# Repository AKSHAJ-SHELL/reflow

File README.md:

# reflow

**An early AI PCB design agent with a verifier that checks its work.**

You describe a small board. An AI drafts it. A verifier written by a person, not by the AI, checks the draft and explains every mistake in plain English. The AI never picks a part number.

> **This is an alpha.** It handles simple, low-speed boards, and it has real gaps. Read [Limits](#limits) and [Risks](#risks) before trusting anything it makes.

## This project grows as I learn

I'm learning electronics while I build this, and reflow only knows what I understand well enough to write a check for. The more I learn, the more the base of reflow will reflect it.

| Stage | What reflow can check | State |
|---|---|---|
| Low-speed boards: I²C sensors, EEPROMs, LEDs | connections, datasheet pin maps, decoupling and pull-ups | **built, and limited** |
| Power and analog: current limits, trace width, heat | | planned |
| High-speed and RF: impedance, return paths, length matching | | planned |
| FPGA boards: power sequencing, many rails, BGA | | planned |
| Chip design (Verilog) | whether the verifier-first idea carries over at all | an idea, not decided |

Anything marked planned doesn't exist yet. If you know more than I do, corrections are the most useful thing you can send.

## What works today

| Part | What it does | State |
|---|---|---|
| `reflow check` | Checks any KiCad schematic for 5 kinds of mistake | works |
| `reflow design` | Model → board code → compile → verify → fix, up to 3 attempts | works on simple boards |
| Part resolver | Finds real parts in a local copy of the JLCPCB catalog | works; some of it is awaiting my review |
| `reflow tui` | The guided way to design a board, step by step | new; one full run so far |
| `reflow learn` | Find the AI's bug in a local web app, run two circuit simulations, sign off | works; simulations awaiting my review |
| `reflow export` | Runs KiCad DRC, then writes gerbers, drill, placement and BOM | works; often refuses (see Limits) |
| `reflow report` | Writes up every attempt, error and sign-off | works |

**What has actually been tested:**
- **Eval, 2026-10-28:** 5 simple boards × 3 runs, on one model (Sonnet, through Claude Code). 12 of 15 runs gave a verifier-clean board on the first attempt, with 0 part numbers from outside the resolver. The AMS1117 regulator failed all 3. An AI agent drafted the boards' expected results and I checked them on 2026-10-31, after this run, so this run's file still says `undecided`. It's a progress check on simple boards I chose, not a benchmark. The results: [evals/results/20261028T161716Z.json](evals/results/20261028T161716Z.json).
- **One real run through the TUI, 2026-11-06:** an INA226 power monitor ([boards/opi-power-demo](boards/opi-power-demo)). It went from a prompt to a verifier-clean schematic on the first attempt, with 0 KiCad ERC violations, and an electrical mentor looked over the schematic informally. It hasn't been routed, exported or built, and its `rules.toml` wasn't enforced (see Limits).
- **No board designed by reflow has been fabricated and tested yet.**

## Try it: check a schematic (5 minutes, macOS)

You need [Homebrew](https://brew.sh). No AI or API key is involved in this part.

```bash
brew install --cask kicad
brew install uv
git clone https://github.com/AKSHAJ-SHELL/reflow
cd reflow
uv venv --python 3.14 .venv
source .venv/bin/activate
uv pip install -e .
```

Run it on a board with a planted bug, then on a good one:

```bash
reflow check fixtures/bad_series_cap
```

```bash
reflow check fixtures/sensor_good
```

The first one reports:

```
✗ ERROR  decoupling.series   C1, U1
  C1 sits in series between +3.3V and U1.8; U1 only gets power through a
  capacitor, which blocks DC.
  why:  A capacitor blocks DC, so the chip never gets steady power and won't
        turn on. Decoupling caps go in parallel, power to ground, to absorb fast
        current spikes at the chip.
  fix:  Connect U1.8 directly to +3.3V, then rewire C1 so one pin is on +3.3V
        and the other is on GND.
```

Then point it at your own board:

```bash
reflow check path/to/your/board.kicad_sch
```

## Design a board

**One-time setup.** Run these from the `reflow` folder (every tool and setting is in [SETUP.md](SETUP.md)):

```bash
brew install node oven-sh/bun/bun
npm ci --prefix tools/tscircuit
export PATH="$PWD/tools/tscircuit/node_modules/.bin:$PATH"
uv pip install -e '.[learn,tui]'
reflow parts update    # downloads the JLCPCB parts catalog, about 1.5 GB
```

The `export PATH` line lasts for one terminal session. Add it to `~/.zshrc`, with the full path, to keep it.

You also need [Claude Code](https://claude.com/claude-code), installed and logged in. reflow uses your login, so no API key is needed.

**Then make a folder for your board and open reflow there:**

```bash
mkdir -p ~/boards/my-board && cd ~/boards/my-board && reflow tui
```

The screen walks you through it, with an AI helper on the right you can ask anything:

1. **Say what you want,** and type the exact part number of the main chip. reflow never picks one for you.
2. **Drag in the chip's datasheet PDF.** The helper can then search it and cite pages.
3. **Draft the plan** and answer its questions. Press **Re-plan with my answers** until it's right, then **Accept plan**.
4. **Write your `rules.toml`:** one rule for each thing the datasheet asks for. reflow gives you a template and checks it. Ask the helper if a section confuses you.
5. **Run the design.** The AI gets up to 3 attempts.
6. **Run `reflow check`.** If it fails, open it in KiCad and learn mode, work out what went wrong, type the fix and run it again.

**← Back** (or Ctrl+B) goes back a step, and Ctrl+Q quits. Everything is saved in the folder, so you can close it and pick up later.

## All commands

| Command | What it does |
|---|---|
| `reflow check PATH` | Check a `.kicad_sch`, a `.kicad_pro` or a project folder. Add `--json` for JSON, or `--strict` to fail on warnings. |
| `reflow tui [FOLDER]` | Design a board step by step. Needs `[tui]` and Claude Code. |
| `reflow design --spec S --plan P --run-dir D` | Design without the TUI, from a spec and plan you wrote. |
| `reflow learn RUN` | Open a finished run in your browser: find the bug, simulate, sign off. Needs `[learn]`. |
| `reflow export RUN` | Run DRC and write fab files to `RUN/out`. |
| `reflow report RUN` | Write `report.md` and `report.json` for a run. |
| `reflow rules check FILE` | Check a `rules.toml` against its parts' pins. |
| `reflow parts update` | Download or refresh the JLCPCB parts catalog. |
| `reflow eval` | Run the eval boards. Add `--only NAME` for one, or `--repeat N`. |

`reflow check` exits `0` when clean, `1` on errors, and `2` for a tool or input problem. Add `--help` to any command for the details.

**Without the TUI**, each folder in `evals/` has a ready spec and plan:

```bash
reflow design --spec evals/mcp9808_breakout/spec.json --plan evals/mcp9808_breakout/plan.json --run-dir runs/mcp9808
```

```bash
reflow learn runs/mcp9808
```

```bash
reflow export runs/mcp9808
```

To use an API instead of Claude Code, see [SETUP.md](SETUP.md#3-a-model).

## Limits

**What it can design**
- **Simple, low-speed, 2-layer boards only:** I²C sensors, EEPROMs, LEDs, a regulator, about 20 parts.
- **Microcontrollers, USB, DDR, Ethernet and RF are out.** There's no high-speed check of any kind.
- **Regulators are shaky.** The AMS1117 failed every eval run on a pin-map question that's still open.

**What the checks miss**
- **"Passed" is a narrow claim.** It means the board compiled and has no violations of the few rules below. It doesn't mean the board works.
- **Only 5 kinds of schematic mistake are caught** (`decoupling.series`, `decoupling.missing`, `i2c.missing_pullup`, `i2c.duplicate_pullup`, `address.floating`), plus pin-map errors on AI boards and one draft rule (`i2c.pullup_rail`). It doesn't replace KiCad's ERC and DRC; run both.
- **Your `rules.toml` doesn't fail a board yet.** The AI is told your rules, but nothing checks the board against them. A board can say `passed` while breaking one (task R-10).
- **I²C checks find the bus by pin name.** A chip that names its pins differently, like the LIS3DH's `SPC`/`SDI`, skips those checks without telling you.
- **No SPI or UART checks.**
- **No current, heat or analog layout checks.** Trace width and Kelvin connections aren't checked. Check them in KiCad.
- **Only two simulations exist** (decoupling and I²C rise time). They use assumed values, shown next to each graph.

**Parts**
- **JLCPCB catalog only.** You can't use another vendor's library yet.
- **The catalog is a snapshot,** so stock and prices can be out of date.

**Routing and platform**
- **Routing is tscircuit's autorouter.** It sometimes breaks a length limit or can't finish, and then `reflow export` refuses. That's deliberate.
- **KiCad 10, single-sheet schematics.** The full flow has only been run on macOS.

## Risks

- **Don't order a board on reflow's word.** Review the schematic and layout yourself against the datasheets. A wrong board costs money and can damage whatever it's plugged into.
- **The AI's code runs on your computer** with your permissions. Its board code is compiled locally as tscircuit TSX, and it isn't sandboxed yet. If you use an API key, that code could reach it (task CI-06). Don't run reflow on a machine holding secrets you can't afford to lose. Details: [docs/REVIEWING.md](docs/REVIEWING.md#4-known-risks-in-the-code-today).
- **Your data goes to the model provider.** Your request, plan and answers, and the parts of your datasheet the helper reads, are sent to Claude or whichever API you set. Don't use it on confidential designs.
- **The local learn server has a known gap.** It only listens on your own machine, but it doesn't check the Host header yet, so a malicious website could try to reach it while it's running (task CI-07). Close it when you're done.
- **AI usage counts against your account.** Runs use your Claude Code plan or your API credits.
- **Some code hasn't had a full human review.** I hand-wrote the core rules and design loop, and AI agents wrote much of the plumbing. Items marked *awaiting human review* in [TASKS.md](TASKS.md) are agent-written and not yet signed off: the resolver's category logic, pin binding, the simulation testbenches and `i2c.pullup_rail`.
- **Expect breaking changes.** File formats and commands can change between versions.

## How it works

```
your request + datasheet ─▶ plan (you confirm) ─▶ part resolver (JLCPCB catalog)
        ─▶ AI writes board code ─▶ compile ─▶ VERIFIER ──fail, up to 3 tries──▶ back to the AI
                                                  │ pass
                                                  ▼
                 you review and sign off ─▶ route check + DRC ─▶ gerbers · BOM · schematic · report
```

More detail: [docs/02-architecture.md](docs/02-architecture.md).

## Folder guide

| Path | What's there |
|---|---|
| `reflow/` | The package: CLI, compile, verifier, routing check, export, TUI |
| `reflow/rules/` | The verifier's rules, one file per family |
| `reflow/harness/` | The design loop: attempts, feedback to the model, when to stop |
| `reflow/parts/` | Parts catalog, resolver, KiCad pin maps |
| `reflow/learn/` | Learn mode's server (`web/` is its source) |
| `prompts/` | The model prompts, as files |
| `boards/` | Sample board projects, including the INA226 demo |
| `evals/` | The boards the design loop is measured on |
| `fixtures/` | KiCad boards with known answers; one planted bug per bad board |
| `tests/` | Tests for every stage |
| `docs/` | Design docs, read in order 00 → 08 |
| `TASKS.md`, `PROGRESS.md` | What's planned, and a log of what happened, including failures |

## Contributing

- **Send a board that died.** Open an issue with the KiCad files and what went wrong. It could become a fixture and maybe a rule.
- **Tell me what's wrong.** Mistakes in the rules or in this README are the most useful reports.
- Plumbing PRs (CLI, exporters, API clients) are welcome. [AGENTS.md](AGENTS.md) has the rules every contributor, human or AI, follows. Never weaken a test to make it pass.

## License

**reflow doesn't have a license yet,** so for now no one else has permission to reuse the code. I plan to open-source it and will add a `LICENSE` file when I've chosen one.

reflow is an independent project, not affiliated with any commercial PCB tool.

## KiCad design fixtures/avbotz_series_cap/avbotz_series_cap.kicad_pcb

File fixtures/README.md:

# fixtures/: boards with known answers (OWNER: HUMAN)

Each folder is a KiCad project (`<name>.kicad_sch/.kicad_pro/.kicad_pcb`) plus `expected.toml`:

```toml
violations = ["decoupling.series"]      # exact set of rule IDs; [] for good boards
pin_net  = { "U1.4" = "GND" }           # optional hand-checked nets
same_net = [["J1.2", "U1.1"]]           # optional
```

Good: `blinky_good`, `sensor_good`. Bad (one planted bug each): `bad_series_cap`, `bad_no_pullups`, `bad_floating_addr`.

**Make one:** `tools/new_fixture.sh <src> <dst>`, open via the `.kicad_pro`, plant one bug, write `expected.toml`.

**Must never:** be created, edited or deleted by an agent; contain more than one planted bug; be opened by double-clicking the `.kicad_sch` (creates "Untitled" files).

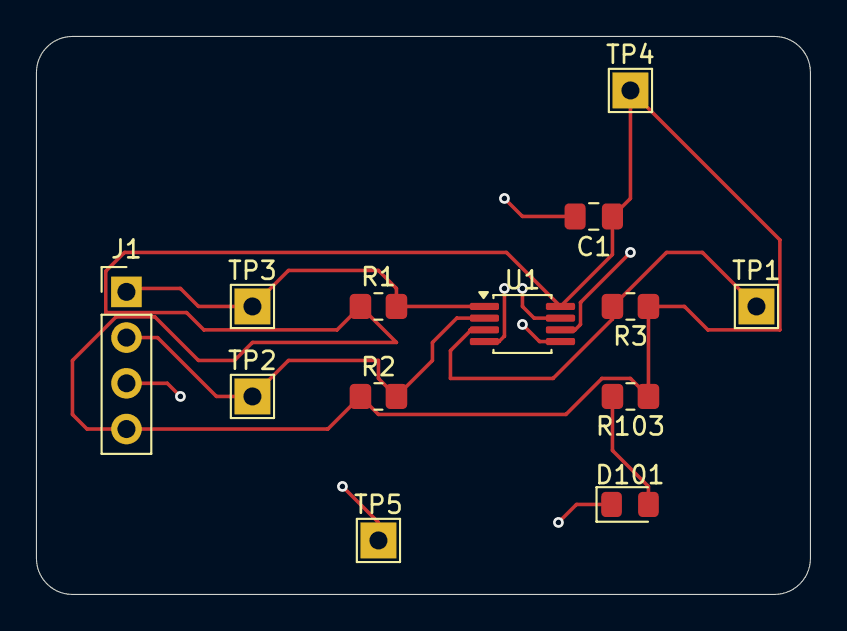
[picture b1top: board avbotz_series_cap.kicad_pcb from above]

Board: 2 copper layers, 43.0 x 31.0 mm, 13 parts (0 on the bottom side), 6 nets.

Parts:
C1: 0.1uf; C_0805_2012Metric_Pad1.18x1.45mm_HandSolder
D101: 3v3_red; LED_0805_2012Metric_Pad1.15x1.40mm_HandSolder
J1: Conn_01x04_Pin; PinHeader_1x04_P2.54mm_Vertical
R1, R2: 4k7; R_0805_2012Metric_Pad1.20x1.40mm_HandSolder
R3: 10k; R_0805_2012Metric_Pad1.20x1.40mm_HandSolder
R103: 270R; R_0805_2012Metric_Pad1.20x1.40mm_HandSolder
TP1, TP2, TP3, TP4, TP5: TestPoint; TestPoint_THTPad_2.0x2.0mm_Drill1.0mm
U1: MCP9808_MSOP; MSOP-8_3x3mm_P0.65mm

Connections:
+3.3V: C1.1, J1.4, R1.1, R2.1, R3.1, R103.1, TP4.1 (1_1), U1.8 (V_{DD})
/SCL: J1.2, R2.2, TP2.1 (1_1), U1.2 (SCL)
/SDA: J1.1, R1.2, TP3.1 (1_1), U1.1 (SDA)
GND: C1.2, D101.1 (K), J1.3, TP5.1 (1_1), U1.4 (GND), U1.5 (A2), U1.6 (A1), U1.7 (A0)
unnamed: D101.2 (A), R103.2
unnamed: R3.2, TP1.1 (1_1), U1.3 (Alert)

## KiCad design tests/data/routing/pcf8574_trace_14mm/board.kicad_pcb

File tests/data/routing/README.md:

# Routing inputs (X-01, X-04)

`mcp9808_fixed.tsx`: the MCP9808 eval board as fixed in learn mode (the real AI draft of eval run
20261022T193720Z, attempt 1, relabelled to the datasheet pinout and wired; it verifies clean).

tscircuit's autorouter runs inside `tsci export`. It gives a decoupling cap's traces a 1 mm
maximum length (`DEFAULT_MAX_DECOUPLING_TRACE_LENGTH_MM` in @tscircuit/core), and skips routing
the whole board when automatic placement leaves the cap farther than that from the pin. As
written, this board doesn't route. With `maxDecouplingTraceLength="3mm"` on C1, every connection
routes and C1's trace to VDD is 2.89 mm. With 2 mm it still doesn't route (tsci 0.0.2768).

2026-10-27: the limit covers both of a decoupling cap's traces, including its ground side to the
nearest GND pad. With 3 mm, placement missed by about 0.5 mm on 3 of 5 eval boards
(run 20261028T004800Z: 3.46–3.56 mm), and routing was skipped. The codegen prompt now asks for 5 mm.

Hole-clearance inputs (2026-10-27), exported .kicad_pcb files from real eval runs (Sonnet 5.5):
- `at24c02_via_0198mm.kicad_pcb` (run 20261028T010434Z): a via 0.198 mm from the SCL track. Under
  JLCPCB's "Via hole to Track" 0.2 mm this is a real violation.
- `ams1117_via_0216mm.kicad_pcb` (same run, attempt 2): a via 0.216 mm from U1 pad 1. It passes
  JLCPCB's 0.2 mm via rule; KiCad's 0.25 mm default flagged it.
- `mcp9808_routed_headers.kicad_pcb` (run 20261028T004800Z): routed, with J1's plated through-holes
  next to tracks (closest 1.25 mm), used to show the PTH rule applies to PTH pads.

Board-size input (2026-10-27): `pcf8574_40x30.tsx` is the PCF8574 eval draft from run
20261028T010434Z (Sonnet 5.5, attempt 1), unchanged. The model drew a 40 x 30 mm board and set
pcbX/pcbY by hand; J1 sits 0.56 mm and J2 4.64 mm past the edge, and tscircuit skipped routing
for the placement errors. With `<board>` (no width or height) and no pcbX/pcbY, tscircuit places
the parts and sizes the board around them (23.28 x 21.875 mm, tsci 0.0.2768), every part sits
inside the edge, and all 12 nets route. Our DRC still finds 2 router vias under JLCPCB's 0.2 mm
via-to-track rule on that board. Keeping the model's placement with no size also fits, but its
decoupling traces come out 8.35 and 8.98 mm, over the 5 mm limit. So the codegen prompt asks for
no size (unless the spec gives one) and no hand placement.

Via inputs (2026-10-27): `at24c02_draft.tsx` (run 20261028T010434Z) and `pcf8574_unsized.tsx`
(run 20261028T025622Z) are real Sonnet 5.5 drafts, unchanged. tscircuit's vias are 0.3 mm on a
0.2 mm drill, and the router keeps ~0.1 mm of copper from a via to a track, so the hole lands
0.198 mm (AT24C02) and 0.159 mm (PCF8574) from a track, under JLCPCB's 0.2 mm. The PCF8574 also
reports a 0.1651 mm via on some runs, not all. With `minViaPadDiameter="0.4mm"` on the board
(0.1 mm ring), both route with 0 DRC errors, 4 of 4 runs each, and the MCP9808, AMS1117
attempts 1–3 and LED boards still route with 0 errors.

Trace-length inputs (2026-10-28), exported boards from run 20261028T161716Z (Sonnet 5.5), each
folder holding circuit.json, board.kicad_pcb, board.kicad_pro, board.kicad_dru and the draft TSX,
unchanged: every net is copper and our DRC has 0 errors, but tscircuit's
`pcb_trace_too_long_error` says a decoupling cap's trace is over the 5 mm asked for.
- `mcp9808_trace_6mm/` (run 3): C1.pin1 to J1.pin1 on V3_3, 6.05 mm.
- `pcf8574_trace_14mm/` (run 2): C1.pin2 to U1.A0 on GND, 14.01 mm (the cap's ground side; U1.A0
  is tied to GND for address 0x20).

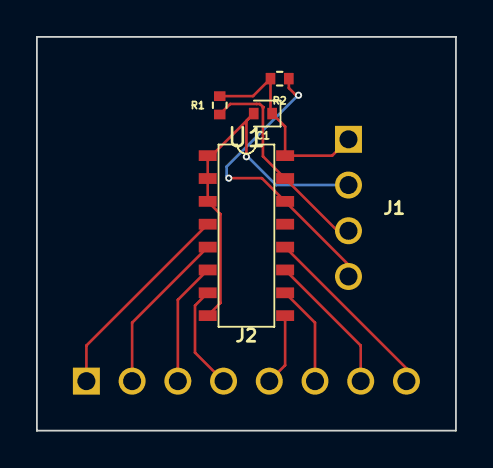
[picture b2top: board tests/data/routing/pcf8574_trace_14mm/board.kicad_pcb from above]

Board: 2 copper layers, 23.3 x 21.9 mm, 6 parts (0 on the bottom side), 12 nets.

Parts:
C1: 100nF; CL05B104KB54PNC
J1: J1; HX_PZ2_54-1x4P_ZZ
J2: J2; PZ254V-11-08P
R1, R2: 4.7kΩ; 0402WGF4701TCE
U1: PCF8574T/3,518; PCF8574T_3_518

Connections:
GND: C1.2, J1.2, U1.1, U1.2, U1.3, U1.8
P0: J2.1, U1.4
P1: J2.2, U1.5
P2: J2.3, U1.6
P3: J2.4, U1.7
P4: J2.5, U1.9
P5: J2.6, U1.10
P6: J2.7, U1.11
P7: J2.8, U1.12
SCL: J1.4, R2.1, U1.14
SDA: J1.3, R1.1, U1.15
V3_3: C1.1, J1.1, R1.2, R2.2, U1.16

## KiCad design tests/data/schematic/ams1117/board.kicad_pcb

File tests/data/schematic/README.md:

# Schematic inputs (O-04)

Real boards from `reflow eval --repeat 3` run 20261028T161716Z (Sonnet 5.5), run 1 of each eval:
the attempt's `circuit.json`, `board.kicad_pcb` and `board.kicad_pro` from its build folder, and a
copy of the eval's `rules.toml` (its `[[part]]` names each chip's KiCad symbol). Unchanged.

- `mcp9808/`, `pcf8574/`, `at24c02/`: attempt 1, verify clean. Our schematic of each has 0 KiCad ERC
  errors and 0 warnings, `reflow check` on it is clean, and its nets are circuit.json's and the PCB's.
- `pcf8574/tscircuit.kicad_sch`: tscircuit's own export of the same board. KiCad ERC finds 21 errors
  and 87 warnings (wire ends 0.06–0.09 mm short of pins, off the 1.27 mm grid; invented symbol
  libraries), J2 and P0–P7 are disconnected, and GND is split in two.
- `led/`: attempt 1. tscircuit's LED has the anode on pad 1; KiCad's LED symbol has the cathode on
  pin 1, so the schematic is refused (the KT-0603R cathode pad is a TO CHECK line in expected.toml).
  No rules.toml: the eval has none.
- `ams1117/`: attempt 3. The board's U1 has pin 4 (the tab); KiCad's AMS1117-3.3 has 3 pins (V-12).

kicad-cli writes `.kicad_prl` next to what it opens, so tests work on copies.

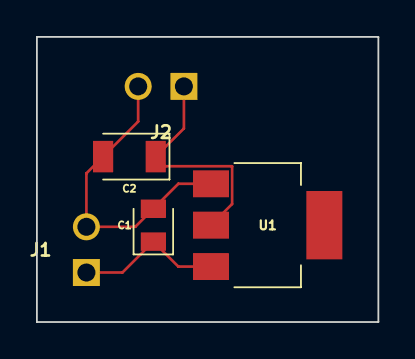
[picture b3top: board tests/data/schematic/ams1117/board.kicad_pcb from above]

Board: 2 copper layers, 19.0 x 15.8 mm, 5 parts (0 on the bottom side), 3 nets.

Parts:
C1: 10uF; CL21A106KAYNNNE
C2: 22uF; CL31A226KAHNNNE
J1: J1; PZ254V-11-02P
J2: J2; PZ254V-11-02P
U1: AMS1117-3.3; AMS1117-3_3

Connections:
GND: C1.2, C2.2, J1.2, J2.2, U1.1
V3_3: C2.1, J2.1, U1.2
V5: C1.1, J1.1, U1.3

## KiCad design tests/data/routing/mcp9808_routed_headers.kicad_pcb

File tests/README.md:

# tests/

| File | What | Needs KiCad |
|---|---|---|
| `conftest.py` | Finds every fixture, exports a fresh netlist per test | yes |
| `test_netlist.py` | Invariants + hand-checked nets + expected violations per fixture | yes |
| `test_cli.py` | `reflow check` exit codes and output | yes (skips if missing) |
| `test_catalog.py` | `parse_value`, `CatalogPart` defaults, and that the jlcsearch client and cache are gone | no |
| `test_contracts.py` | Frozen schemas, strict example parsing, stub honesty | no |
| `test_circuit_netlist.py` | `circuit.json` → `Netlist` on recorded boards (`data/circuit_json/`), the rules on that netlist, and malformed input | no |
| `test_pcb_nets.py` | `.kicad_pcb` pad nets: tscircuit export vs its `circuit.json`, syntax and error cases | no |
| `test_pinmap.py` | Pin maps from ST pin data and KiCad symbols (`data/pinmaps/`, licences beside them): MCP9808 vs its datasheet, STM32F103C8 across sources, disagreement reporting | installed-library case only (skips if missing) |
| `test_verifier.py` | The design verifier on recorded `circuit.json` boards: report shape, required `bind`, refuses `.kicad_sch` | no |
| `test_design_wiring.py` | `reflow design` from config: scripted model, real tsci and verifier, fake catalog; config and catalog errors | tsci for the end-to-end cases (skips if missing) |
| `test_parts_snapshot.py` | `reflow parts update` on a six-part split-archive fixture (`data/snapshot/`) over file:// URLs: install, CRC and format checks, old database kept on failure | no |
| `test_local_catalog.py` | Local-snapshot queries on 27 real rows (`data/parts_db/`): values, tolerance, voltage, headers, MPN prefix, category mapping, the MCP9808 plan through the resolver | no |
| `test_evals.py` | Structure of every `evals/` board: strict spec and plan, named parts verbatim in the request, D-6a headers, expected.toml agrees with the plan | no |
| `test_eval_runner.py` | The eval runner with a scripted model, real tsci and verifier, and the parts fixture: pass rates, foreign part numbers, expectation misses, errors, go/no-go, results file, `reflow eval` | tsci (skips if missing); about 2 minutes |
| `test_project_rules.py` | `rules.toml` parsing and `reflow rules check`: required why/source, field errors, unknown pins, uncovered power/reset/boot pins | no |
| `test_rules_prompt.py` | Project rules rendered for the codegen/fix prompts (no why/source), `reflow design` resolving and checking `rules_file`, `[[part]]` pin maps in `reflow rules check`; one test is red until `docs/proposals/V-22-loop-HUMAN.patch` is applied | no |
| `test_pinbind.py` | V-12 pin binding on the first real board (`data/real_runs/`): its wrong MCP9808 pinout is reported pin by pin, the corrected board binds clean, bound power pins let decoupling run, unidentified / unmapped chips are errors | no |
| `test_integration.py` | Real tsci + kicad-cli + rules, and the design loop with a scripted model (inputs in `data/integration/`) | yes, and tsci (skips if missing) |

Run: `pytest -q`. **Never weaken a test** (docs/agents/04-testing-rules.md).

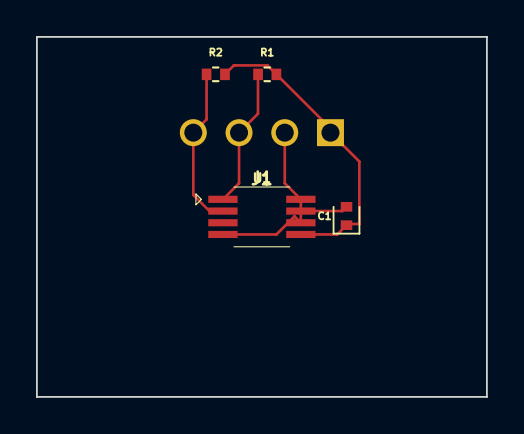
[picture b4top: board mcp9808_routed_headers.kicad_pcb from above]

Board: 2 copper layers, 25.0 x 20.0 mm, 5 parts (0 on the bottom side), 4 nets.

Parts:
C1: 100nF; CL05B104KB54PNC
J1: J1; HX_PZ2_54-1x4P_ZZ
R1, R2: 4.7kΩ; 0402WGF4701TCE
U1: MCP9808T-E/MS; MCP9808T-E_MS

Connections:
GND: C1.2, J1.2, U1.4, U1.5, U1.6, U1.7
SCL: J1.4, R2.1, U1.2
SDA: J1.3, R1.1, U1.1
V3_3: C1.1, J1.1, R1.2, R2.2, U1.8

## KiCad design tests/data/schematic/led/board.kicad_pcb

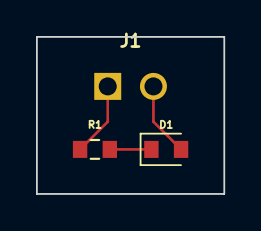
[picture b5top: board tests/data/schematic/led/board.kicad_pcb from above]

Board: 2 copper layers, 10.4 x 8.7 mm, 3 parts (0 on the bottom side), 3 nets.

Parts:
D1: KT-0603R
J1: J1; PZ254V-11-02P
R1: 1kΩ; 0603WAF1001T5E

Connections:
.R1 > .pin2 to .D1 > .anode: D1.1, R1.2
GND: D1.2, J1.2
V3_3: J1.1, R1.1

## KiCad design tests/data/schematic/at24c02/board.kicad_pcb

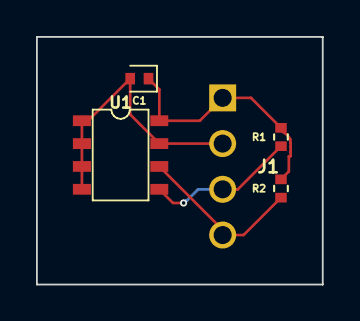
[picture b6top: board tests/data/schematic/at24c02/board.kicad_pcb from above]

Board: 2 copper layers, 15.9 x 13.8 mm, 5 parts (0 on the bottom side), 4 nets.

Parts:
C1: 100nF; CL05B104KB54PNC
J1: J1; HX_PZ2_54-1x4P_ZZ
R1, R2: 4.7kΩ; 0402WGF4701TCE
U1: AT24C02

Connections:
GND: C1.2, J1.2, U1.1, U1.2, U1.3, U1.4, U1.7
SCL: J1.4, R2.1, U1.6
SDA: J1.3, R1.1, U1.5
V3_3: C1.1, J1.1, R1.2, R2.2, U1.8
